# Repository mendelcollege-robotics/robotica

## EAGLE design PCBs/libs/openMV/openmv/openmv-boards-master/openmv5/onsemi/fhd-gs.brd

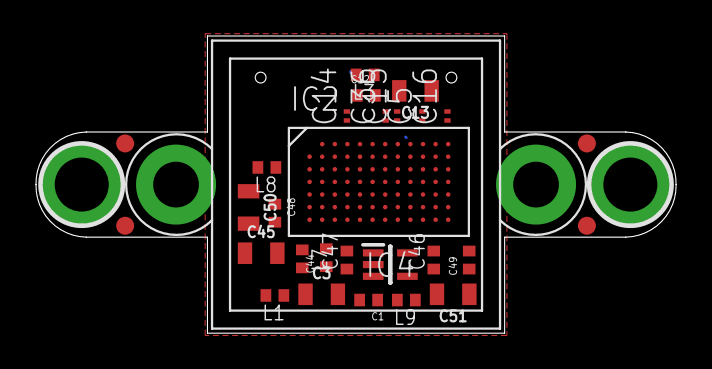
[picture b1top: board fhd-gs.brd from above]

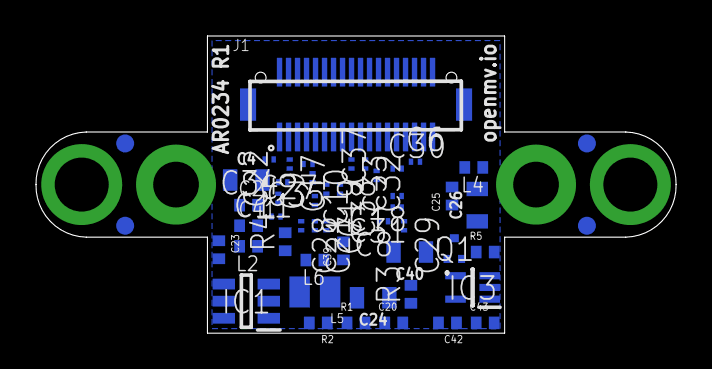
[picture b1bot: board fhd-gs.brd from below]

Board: 6 copper layers, 35.6 x 16.5 mm, 80 parts (51 on the bottom side), 40 nets.

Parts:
C1, C2, C12, C23, C25, C39, C41, C42, C43, C44, C46, C47, C48, C49: 4.7uF; 0402
C3, C4, C13, C24, C26, C40, C45, C50, C51: 22uF; 0805
C5, C6, C7, C8, C9, C10, C11, C14, C15, C16, C17, C18, C19, C21, C22, C27, C28, C29, C30, C31, C32, C33, C34, C35, C36, C37, C38: 0.22uF; C0201
C20: 6.8pF; 0402
FD1, FD2, FD3, FD4, FD5, FD6, FD7, FD8: FIDUCIAL1X2; FIDUCIAL-1X2
H1: LENSMOUNT20MM; LENSMOUNT-20MM
IC1: TLV62568PDDCR; SOT95P280X110-6N
IC2: AR0234CSSC00SUKA0
IC3, IC4: MIC5365-2.8YC5-TR; SOT65P210X110-5N
J1: DF12-36-DP
L1, L2, L3, L4, L6, L7, L8, L9: 100; 0402
L5: MAKK2016T2R2M; INDC2016X100N
Q1: SSM3J15FV,L3F; SSM3J15FVL3F
R1, R2, R5: 100K; R0402
R3: 10K; R0402
R4: 1.5K; R0402

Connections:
CAP: C41.2, IC2.P$71
DCMI_CLK: IC2.P$82, J1.12
DCMI_D0: IC2.P$62, J1.9
DCMI_D1: IC2.P$75, J1.7
DCMI_D2: IC2.P$76, J1.31
DCMI_D3: IC2.P$50, J1.29
DCMI_D4: IC2.P$36, J1.35
DCMI_D5: IC2.P$37, J1.28
DCMI_D6: IC2.P$14, J1.26
DCMI_D7: IC2.P$51, J1.33
DCMI_D8: IC2.P$39, J1.24
DCMI_D9: IC2.P$27, J1.22
DCMI_FSIN: IC2.P$40, J1.23
DCMI_HSYNC: IC2.P$30, J1.18
DCMI_PCLK: IC2.P$29, J1.14
DCMI_PWDN: J1.25, Q1.1
DCMI_PWDN_INT: IC3.3, Q1.3, R5.1
DCMI_RST: J1.21, R3.2
DCMI_SCL: IC2.P$65, J1.32
DCMI_SDA: IC2.P$53, J1.34
DCMI_VSYNC: IC2.P$18, J1.16
FB: C20.2, IC1.6, R1.1, R2.1
GND: C1.1, C2.1, C3.1, C4.1, C5.2, C6.2, C7.2, C8.2, C9.2, C10.2, C11.2, C12.1, C13.1, C14.2, C15.2, C16.2, C17.2, C18.2, C19.2, C21.2, C22.2, C23.1, C24.1, C25.1, C26.1, C27.2, C28.2, C29.2, C30.2, C31.2, C32.2, C33.2, C34.2, C35.2, C36.2, C37.2, C38.2, C39.1, C40.1, C41.1, C42.1, C43.1, C44.1, C45.1, C46.1, C47.1, C48.1, C49.1, C50.1, C51.1, IC1.2, IC2.P$1, IC2.P$2, IC2.P$4, IC2.P$5, IC2.P$8, IC2.P$13, IC2.P$17, IC2.P$23, IC2.P$24, IC2.P$26, IC2.P$28, IC2.P$43, IC2.P$44, IC2.P$49, IC2.P$54, IC2.P$55, IC2.P$61, IC2.P$64, IC2.P$68, IC2.P$74, IC2.P$77, IC2.P$81, IC3.2, IC4.2, J1.1, J1.3, J1.5, J1.6, J1.8, J1.19, J1.27, R2.2, R4.1, R5.2
RESET_N: IC1.5, IC2.P$66, R3.1
RSVD: IC2.P$69, R4.2
SPI_MISO: IC2.P$52, J1.15
SW: IC1.3, L5.2
VAA: C5.1, C6.1, C7.1, C8.1, C44.2, C45.2, IC2.P$9, IC2.P$12, IC2.P$73, IC2.P$78, L7.1
VAA_PHY: C9.1, C39.2, C40.2, IC2.P$67, L6.1
VAA_PIX: C27.1, C28.1, C29.1, C30.1, C48.2, C50.2, IC2.P$19, IC2.P$25, IC2.P$72, IC2.P$80, L8.1
VCC: C23.2, IC1.4, J1.2, J1.10, J1.20, J1.30, J1.36
VDD: C1.2, C3.2, C14.1, C15.1, C16.1, C17.1, C18.1, C19.1, C21.1, IC2.P$3, IC2.P$7, IC2.P$11, IC2.P$21, IC2.P$42, IC2.P$48, IC2.P$79, L1.1
VDDA: C43.2, C47.2, IC3.1, IC4.1, J1.4, Q1.2
VDDIO: C31.1, C32.1, C33.1, C34.1, C35.1, C36.1, C37.1, C38.1, C49.2, C51.2, IC2.P$6, IC2.P$15, IC2.P$16, IC2.P$22, IC2.P$38, IC2.P$41, IC2.P$60, IC2.P$83, L9.1
VDDIO_PHY: C11.1, C25.2, C26.2, IC2.P$45, L4.1
VDDIO_PHY_REG: C46.2, IC1.1, IC4.5, L4.2
VDDIO_REG: C42.2, IC3.5, IC4.3, L6.2, L7.2, L8.2, L9.2
VDD_DATA: C2.2, C4.2, C22.1, IC2.P$70, L2.1
VDD_PHY: C10.1, C12.2, C13.2, IC2.P$31, L3.1
VDD_REG: C20.1, C24.2, L1.2, L2.2, L3.2, L5.1, R1.2

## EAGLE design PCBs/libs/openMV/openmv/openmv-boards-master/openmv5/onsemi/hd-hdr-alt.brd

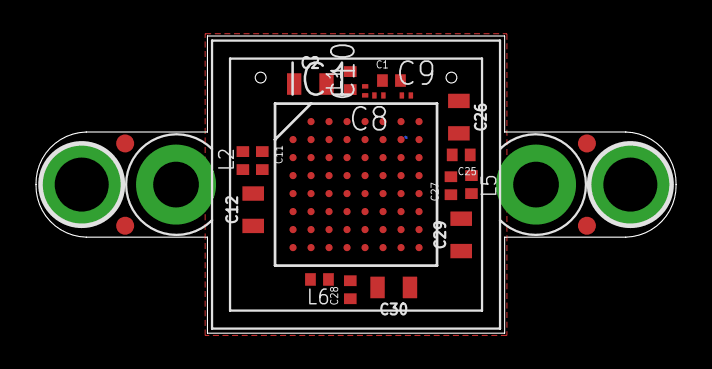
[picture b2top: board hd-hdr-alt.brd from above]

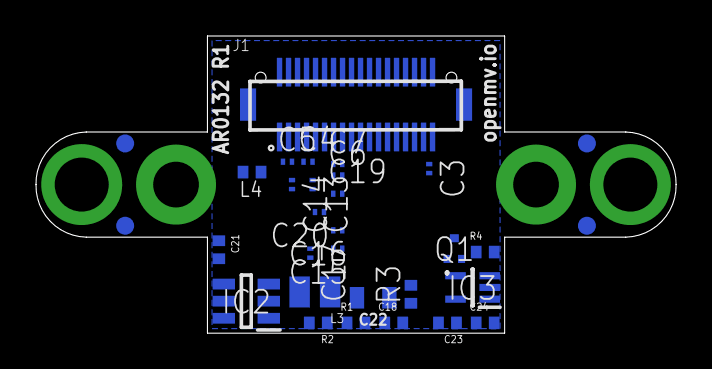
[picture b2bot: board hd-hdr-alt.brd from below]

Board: 6 copper layers, 35.6 x 16.5 mm, 54 parts (31 on the bottom side), 36 nets.

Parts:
C1, C11, C21, C23, C24, C25, C27, C28: 4.7uF; 0402
C2, C12, C22, C26, C29, C30: 22uF; 0805
C3, C4, C5, C6, C7, C8, C9, C10, C13, C14, C15, C16, C17, C19, C20: 0.22uF; C0201
C18: 6.8pF; 0402
FD1, FD2, FD3, FD4, FD5, FD6, FD7, FD8: FIDUCIAL1X2; FIDUCIAL-1X2
H1: LENSMOUNT20MM; LENSMOUNT-20MM
IC1: AR0132AT6C00XPEA0
IC2: TLV62568PDDCR; SOT95P280X110-6N
IC3: MIC5365-2.8YC5-TR; SOT65P210X110-5N
J1: DF12-36-DP
L1, L2, L4, L5, L6: 100; 0402
L3: MAKK2016T2R2M; INDC2016X100N
Q1: SSM3J15FV,L3F; SSM3J15FVL3F
R1: 200K; R0402
R2, R4: 100K; R0402
R3: 10K; R0402

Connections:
DCMI_CLK: IC1.P$16, J1.12
DCMI_D0: IC1.P$56, J1.3
DCMI_D1: IC1.P$57, J1.1
DCMI_D2: IC1.P$58, J1.9
DCMI_D3: IC1.P$59, J1.7
DCMI_D4: IC1.P$48, J1.31
DCMI_D5: IC1.P$49, J1.29
DCMI_D6: IC1.P$50, J1.35
DCMI_D7: IC1.P$51, J1.28
DCMI_D8: IC1.P$40, J1.26
DCMI_D9: IC1.P$41, J1.33
DCMI_D10: IC1.P$42, J1.24
DCMI_D11: IC1.P$43, J1.22
DCMI_FSIN: IC1.P$54, J1.23
DCMI_HSYNC: IC1.P$32, J1.18
DCMI_PCLK: IC1.P$34, J1.14
DCMI_PWDN: J1.25, Q1.1
DCMI_PWDN_INT: IC3.3, Q1.3, R4.1
DCMI_RST: J1.21, R3.2
DCMI_SCL: IC1.P$25, J1.32
DCMI_SDA: IC1.P$26, J1.34
DCMI_VSYNC: IC1.P$33, J1.16
FB: C18.2, IC2.6, R1.1, R2.1
GND: C1.1, C2.1, C3.2, C4.2, C5.2, C6.2, C7.2, C8.2, C9.2, C10.2, C11.1, C12.1, C13.2, C14.2, C15.2, C16.2, C17.2, C19.2, C20.2, C21.1, C22.1, C23.1, C24.1, C25.1, C26.1, C27.1, C28.1, C29.1, C30.1, IC1.P$7, IC1.P$20, IC1.P$22, IC1.P$23, IC1.P$24, IC1.P$27, IC1.P$28, IC1.P$36, IC1.P$44, IC1.P$46, IC1.P$52, IC1.P$55, IC1.P$60, IC2.2, IC3.2, J1.5, J1.6, J1.8, J1.19, J1.27, R2.2, R4.2
RESET_N: IC1.P$63, IC2.5, R3.1
SPI_MISO: IC1.P$35, J1.15
SW: IC2.3, L3.2
VAA: C4.1, C5.1, C25.2, C26.2, IC1.P$14, IC1.P$15, L4.1
VAA_PIX: C13.1, C14.1, C27.2, C29.2, IC1.P$30, IC1.P$31, L5.1
VCC: C21.2, IC2.4, J1.2, J1.10, J1.20, J1.30, J1.36
VDD: C1.2, C2.2, C6.1, C7.1, C8.1, C9.1, C10.1, IC1.P$5, IC1.P$6, IC1.P$13, IC1.P$21, IC1.P$29, L1.1
VDDA: C24.2, IC3.1, J1.4, Q1.2
VDDIO: C15.1, C16.1, C17.1, C19.1, C20.1, C28.2, C30.2, IC1.P$37, IC1.P$45, IC1.P$53, IC1.P$61, IC1.P$62, L6.1
VDDIO_REG: C23.2, IC2.1, IC3.5, L2.2, L4.2, L5.2, L6.2
VDD_PLL: C3.1, C11.2, C12.2, IC1.P$8, L2.1
VDD_REG: C18.1, C22.2, L1.2, L3.1, R1.2

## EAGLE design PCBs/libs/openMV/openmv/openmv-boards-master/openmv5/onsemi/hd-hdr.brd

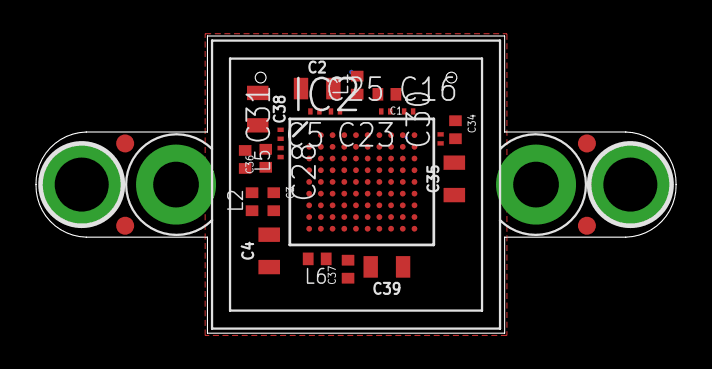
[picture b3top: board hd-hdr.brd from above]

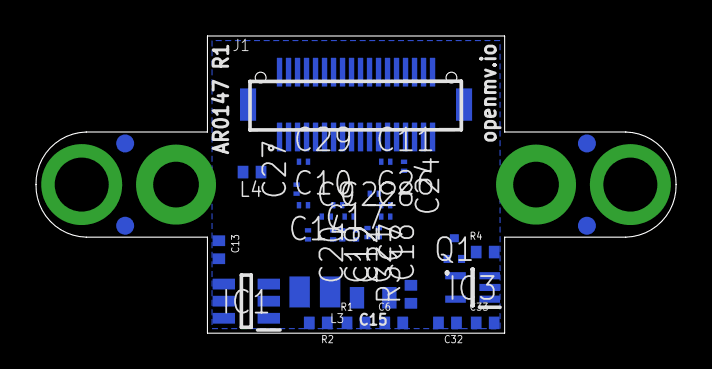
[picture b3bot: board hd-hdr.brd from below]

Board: 6 copper layers, 35.6 x 16.5 mm, 63 parts (36 on the bottom side), 36 nets.

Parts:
C1, C3, C13, C32, C33, C34, C36, C37: 4.7uF; 0402
C2, C4, C15, C35, C38, C39: 22uF; 0805
C5, C7, C8, C9, C10, C11, C12, C14, C16, C17, C18, C19, C20, C21, C22, C23, C24, C25, C26, C27, C28, C29, C30, C31: 0.22uF; C0201
C6: 6.8pF; 0402
FD1, FD2, FD3, FD4, FD5, FD6, FD7, FD8: FIDUCIAL1X2; FIDUCIAL-1X2
H1: LENSMOUNT20MM; LENSMOUNT-20MM
IC1: TLV62568PDDCR; SOT95P280X110-6N
IC2: AR0147ATSC00XUEG5
IC3: MIC5365-2.8YC5-TR; SOT65P210X110-5N
J1: DF12-36-DP
L1, L2, L4, L5, L6: 100; 0402
L3: MAKK2016T2R2M; INDC2016X100N
Q1: SSM3J15FV,L3F; SSM3J15FVL3F
R1, R2, R4: 100K; R0402
R3: 10K; R0402

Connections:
DCMI_CLK: IC2.P$43, J1.12
DCMI_D0: IC2.P$81, J1.3
DCMI_D1: IC2.P$32, J1.1
DCMI_D2: IC2.P$73, J1.9
DCMI_D3: IC2.P$63, J1.7
DCMI_D4: IC2.P$13, J1.31
DCMI_D5: IC2.P$54, J1.29
DCMI_D6: IC2.P$74, J1.35
DCMI_D7: IC2.P$34, J1.28
DCMI_D8: IC2.P$56, J1.26
DCMI_D9: IC2.P$45, J1.33
DCMI_D10: IC2.P$25, J1.24
DCMI_D11: IC2.P$36, J1.22
DCMI_FSIN: IC2.P$79, J1.23
DCMI_HSYNC: IC2.P$57, J1.18
DCMI_PCLK: IC2.P$23, J1.14
DCMI_PWDN: J1.25, Q1.1
DCMI_PWDN_INT: IC3.3, Q1.3, R4.1
DCMI_RST: J1.21, R3.2
DCMI_SCL: IC2.P$15, J1.32
DCMI_SDA: IC2.P$27, J1.34
DCMI_VSYNC: IC2.P$67, J1.16
FB: C6.2, IC1.6, R1.1, R2.1
GND: C1.1, C2.1, C3.1, C4.1, C5.2, C7.2, C8.2, C9.2, C10.2, C11.2, C12.2, C13.1, C14.2, C15.1, C16.2, C17.2, C18.2, C19.2, C20.2, C21.2, C22.2, C23.2, C24.2, C25.2, C26.2, C27.2, C28.2, C29.2, C30.2, C31.2, C32.1, C33.1, C34.1, C35.1, C36.1, C37.1, C38.1, C39.1, IC1.2, IC2.P$3, IC2.P$9, IC2.P$12, IC2.P$16, IC2.P$17, IC2.P$18, IC2.P$24, IC2.P$26, IC2.P$28, IC2.P$33, IC2.P$35, IC2.P$38, IC2.P$42, IC2.P$44, IC2.P$46, IC2.P$48, IC2.P$49, IC2.P$53, IC2.P$55, IC2.P$64, IC2.P$66, IC2.P$76, IC2.P$80, IC2.P$89, IC3.2, J1.5, J1.6, J1.8, J1.19, J1.27, R2.2, R4.2
RESET_N: IC1.5, IC2.P$47, R3.1
SPI_MISO: IC2.P$78, J1.15
SW: IC1.3, L3.2
VAA: C28.1, C29.1, C30.1, C34.2, C35.2, IC2.P$10, IC2.P$19, IC2.P$29, L4.1
VAA_PIX: C31.1, C36.2, C38.2, IC2.P$11, L5.1
VCC: C13.2, IC1.4, J1.2, J1.10, J1.20, J1.30, J1.36
VDD: C1.2, C2.2, C5.1, C7.1, C8.1, C9.1, C10.1, C11.1, C12.1, C14.1, C16.1, IC2.P$1, IC2.P$8, IC2.P$22, IC2.P$65, IC2.P$69, IC2.P$72, IC2.P$77, IC2.P$83, IC2.P$85, L1.1
VDDA: C33.2, IC3.1, J1.4, Q1.2
VDDIO: C18.1, C19.1, C20.1, C21.1, C22.1, C23.1, C24.1, C25.1, C26.1, C27.1, C37.2, C39.2, IC2.P$2, IC2.P$7, IC2.P$20, IC2.P$59, IC2.P$62, IC2.P$75, IC2.P$82, IC2.P$84, IC2.P$86, IC2.P$88, L6.1
VDDIO_REG: C32.2, IC1.1, IC3.5, L4.2, L5.2, L6.2
VDD_PHY: C3.2, C4.2, C17.1, IC2.P$52, L2.1
VDD_REG: C6.1, C15.2, L1.2, L2.2, L3.1, R1.2

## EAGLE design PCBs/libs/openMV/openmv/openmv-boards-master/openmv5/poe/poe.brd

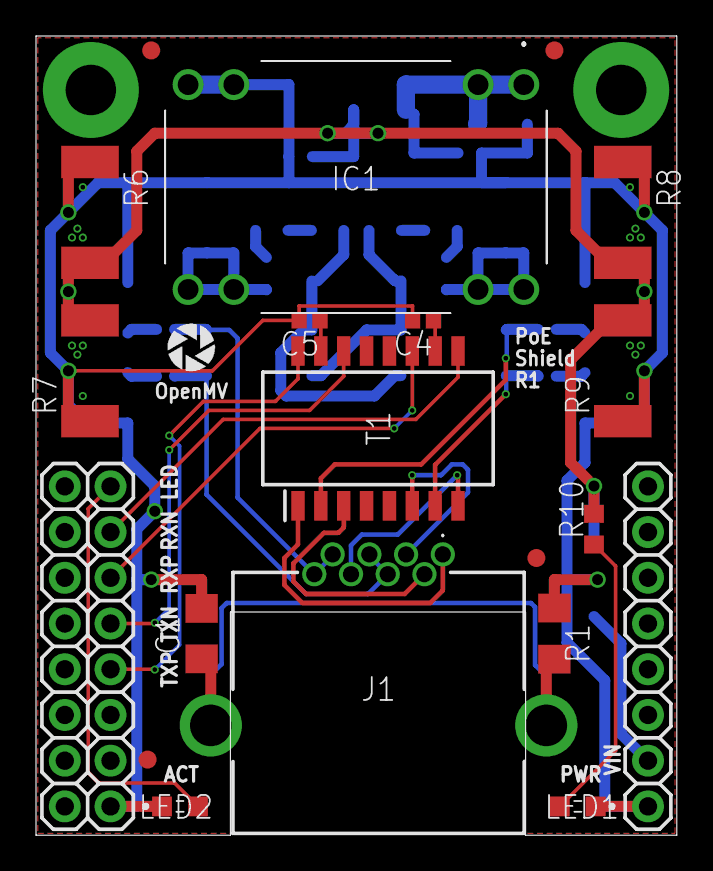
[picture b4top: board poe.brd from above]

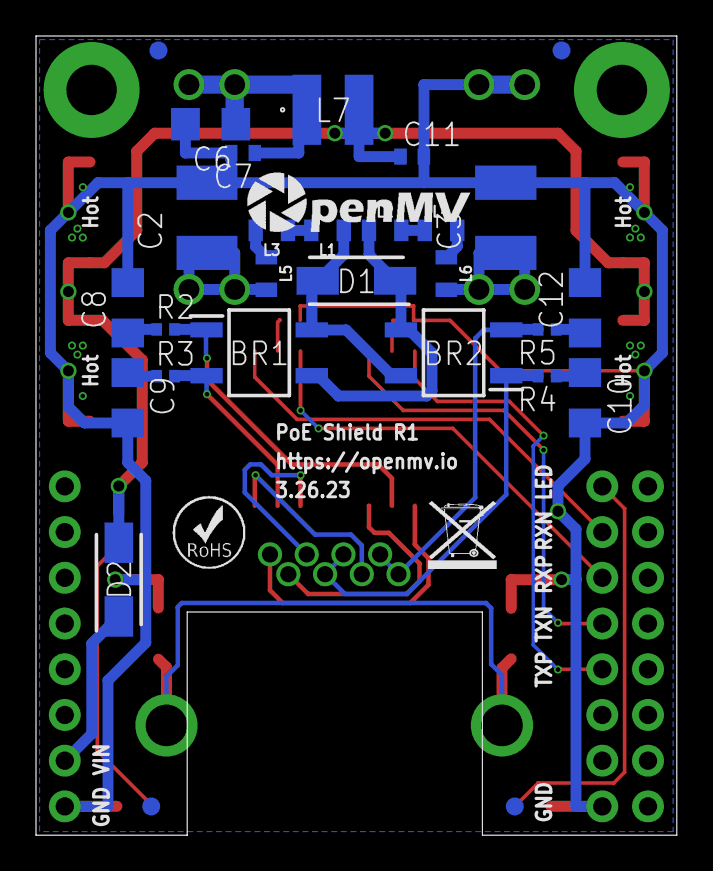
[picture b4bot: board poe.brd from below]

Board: 2 copper layers, 35.6 x 44.4 mm, 51 parts (31 on the bottom side), 33 nets.

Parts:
BR1, BR2: MB6S-TP; SOP254P665X270-4N
C1, C8, C9, C10, C12: 1nF; C1206
C2, C3: 4.7nF; C1812
C4, C5: 0.1uF; 0402
C6: 100uF; C1206
C7, C11: 10uF; C0402
D1: SMAJ58A-13-F; DIOM5226X230N
D2: FM240A; DIOM5025X231N
FD1, FD2, FD3, FD4, FD5, FD6, FD7, FD8: FIDUCIAL1X2; FIDUCIAL-1X2
IC1: AG9905LP
J1: GMJXHT-MM-S-88; GMJXHTMMS88
J2: OPENMV5-BOTTOM
L1, L2, L3, L4, L5, L6: 1K; 0805
L7: VLCF4020T-1R8N1R9; VLCF4020
LED1: LTST-S270KSKT; LTSTS270K
LED2: LTST-S270KGKT; LTSTS270K
R1: 1M; R1206
R2, R3, R4, R5: 75; R0402
R6, R7, R8, R9: 100; R2512
R10: 470; R0603
T1: PT61018PEL; SOIC127P930X565-16N
U$1: WEEE
U$2: ROHS
U$3: OMV-LOGO
U$9: OPENMV-LOGO

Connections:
GND: C1.2, C2.2, C3.2, C4.2, C5.2, C6.2, C7.2, C8.2, C9.2, C10.2, C11.2, C12.2, IC1.3, IC1.4, J2.9, J2.24, LED1.1, LED2.1, R1.1, R6.1, R7.1, R8.1, R9.1
MDI_LED: J2.17, LED2.2
MDI_RX_CT: C4.1, T1.10
MDI_RX_N: J2.18, T1.9
MDI_RX_P: J2.19, T1.11
MDI_TX_CT: C5.1, T1.15
MDI_TX_N: J2.20, T1.14
MDI_TX_P: J2.21, T1.16
POE_VIN_INT_N: C2.1, IC1.7, IC1.8, L5.2
POE_VIN_INT_P: C3.1, IC1.5, IC1.6, L6.2
POE_VIN_N: BR1.4, BR2.4, D1.2, L1.1
POE_VIN_N0: L1.2, L3.1
POE_VIN_N1: L3.2, L5.1
POE_VIN_P: BR1.3, BR2.3, D1.1, L2.1
POE_VIN_P0: L2.2, L4.1
POE_VIN_P1: L4.2, L6.1
RX_N: J1.6, T1.8
RX_P: J1.3, T1.6
SHIELD_GND: C1.1, J1.MH1, J1.MH2, R1.2
TX_N: J1.2, T1.3
TX_P: J1.1, T1.1
VA1: BR1.1, R2.2, T1.2
VA1_ISO: C8.1, R2.1
VA2: BR1.2, R3.2, T1.7
VA2_ISO: C9.1, R3.1
VB1: BR2.1, J1.4, J1.5, R4.2
VB1_ISO: C10.1, R4.1
VB2: BR2.2, J1.7, J1.8, R5.2
VB2_ISO: C12.1, R5.1
VDC: C6.1, C7.1, IC1.1, IC1.2, L7.1
VIN: C11.1, D2.2, L7.2, R6.2, R7.2, R8.2, R9.2, R10.2
VIN_INT: D2.1, J2.10
VIN_LED: LED1.2, R10.1

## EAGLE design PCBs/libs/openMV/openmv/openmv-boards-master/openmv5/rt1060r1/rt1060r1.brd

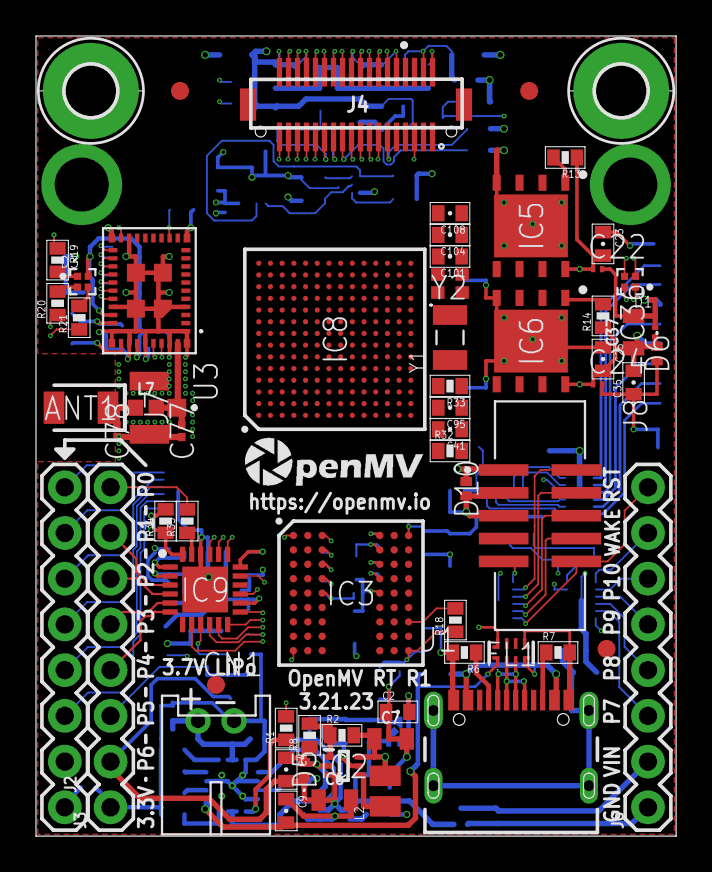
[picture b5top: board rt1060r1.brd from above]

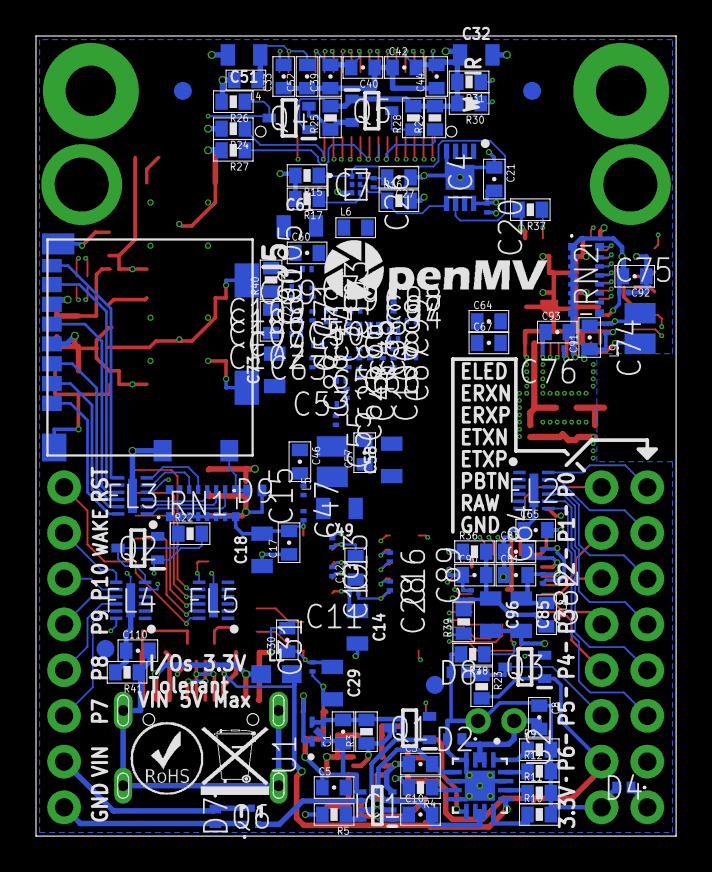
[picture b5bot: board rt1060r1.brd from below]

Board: 8 copper layers, 35.6 x 44.4 mm, 222 parts (153 on the bottom side), 216 nets.

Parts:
ANT1: AMCA31-2R450G-S1F-T3; ANTC3216X140N
C1, C2, C3, C4, C5, C8, C9, C10, C12, C17, C21, C23, C25, C27, C30, C33, C35, C39, C40, C41, C42, C44, C46, C52, C57, C60, C64, C65, C67, C72, C81, C83, C90, C91, C92, C93, C95, C101, C104, C108: 4.7uF; 0402-CAP
C6, C7, C14, C18, C29, C32, C37, C49, C51, C58, C61, C73, C85, C96: 22uF; 0805
C11, C13, C15, C16, C19, C20, C22, C24, C26, C28, C31, C34, C36, C38, C43, C45, C47, C48, C50, C53, C54, C55, C56, C59, C62, C63, C66, C68, C69, C70, C71, C74, C75, C76, C82, C84, C86, C87, C88, C89, C94, C97, C98, C99, C100, C102, C103, C107, C109: 0.22uF; C0201
C77: GRM0335C1H1R5BA01D; CAPC0603X33N
C78: DNP; CAPC0603X33N
C79, C80: 18pF; C0201
C105, C106: 4.7pF; C0201
C110: 1nF; 0402-CAP
CN1: S2B-PH-K-S(LF)(SN); JST-PH-2-THM-RA
D1, D3: UHD1110-FKA-CL1A13R3Q1BBQFMF3; LED_UHD1110-FKA-CL1A13R3Q1BBQFMF3
D2, D4, D5, D6, D7, D8, D9, D10: CPDQT5V0HE-HF; CPDQT5V0HEHF
FD1, FD2, FD3, FD4, FD5, FD6, FD7, FD8: FIDUCIAL1X2; FIDUCIAL-1X2
FL1: ECMF02-4CMX8; ECMF024CMX8
FL2, FL3, FL4, FL5: EMIF06-1005M12; SON40P150X250X65-13N
H1, H2: MOUNT-PAD-ROUND2.8; 2,8-PAD
IC1: LM66200DRLR; SOTFL50P160X60-8N
IC2: AP61300Z6-7; SOTFL50P162X60-6N
IC3: IS42S16160G-6BL; BGA54C80P9X9_800X800X120
IC4: ATECC608B-MAHDA-T; SON50P300X200X60-9N
IC5: IS25LP064D-JKLE-TR; SON127P500X595X80-9N
IC6: IS25LP128F-JKLE-TR; SON127P500X595X80-9N
IC7: MXC4005XC
IC8: MIMXRT106FCVL5B; BGA196C65P14X14_1000X1000X143
IC9: KSZ8081RNDCA-TR; QFN50P400X400X90-25N
J1: USB4105-GF-A; GCT_USB4105-GF-A
J2, J3, J6: DNP; 1X08
J4: DF12-36-DS
J5: USD-1040310811; 1040310811
J7: DNP; 23370191
J8: 3221-10-0300-00; CNC_3221-10-0300-00
L1: 100; 0603
L2: MAKK2016T1R0M; INDC2016X100N
L4, L6, L8: 100; C0402
L5: MAKK2016T4R7M; INDC2016X100N
L7: 3.9NH; 0402
L9: MAKK2016T2R2M; INDC2016X100N
M1, M2: 9774030151R
Q1, Q2, Q3, Q4, Q5: 2N7002KW_R1_00001; SOT65P210X110-3N
Q6: PMXB120EPEZ
R1, R4, R5, R26, R36, R39: 1K; 0402-RES
R2: 200K; 0402-RES
R3, R13, R14, R18, R22, R23, R24, R25, R27, R28, R29, R34: 100K; 0402-RES
R6, R7: 5.1K; 0402-RES
R8: 44.2K; 0402-RES
R9, R33, R37: 10K; 0402-RES
R10: 3.3K; 0402-RES
R11: 46.4K; 0402-RES
R12: 8.2K; 0402-RES
R15, R16, R17: 2.7K; 0402-RES
R19, R20, R21, R35: 220; 0402-RES
R30, R31: 4.7K; 0402-RES
R32: 30K; 0402-RES
R38: 6.49K; 0402-RES
R40: 2.2M; 0402-RES
R41: 1M; 0402-RES
RN1, RN2: EXB-2HV104JV; EXB2HV104JV
U1: MIC5365-3.3YMT-TZ; VREG_MIC5365-3.3YMT-TZ
U2: BQ24075RGTR; QFN50P300X300X100-17N
U3: LBEE5KL1DX-883; XCVR_LBEE5KL1DX-TEMP
U$1: WEEE
U$2: ROHS
U$3: OMV-LOGO
U$4: OMV-LOGO-SMALL
Y1: SC32S-7PF20PPM; XTAL_ABS07-32.768KHZ-7-T
Y2: XRCGB24M000F3M00R0

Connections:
ANT: C77.1, J7.1, L7.2, U3.41
BAT: C8.2, CN1.1, D2.1, U2.2, U2.3
BT_D_WAKE: IC8.L7, U3.39
BT_H_WAKE: IC8.H14, U3.38
BT_REG_ON: IC8.F13, R37.1, U3.14
BT_UART_RX: IC8.C9, U3.3
BT_UART_TX: IC8.B9, U3.2
CC1: J1.A5, R6.1
CC2: J1.B5, R7.1
CHG: R1.1, U2.9
DCDC_LP: IC8.M1, IC8.M2, L5.2
DCDC_PSWITCH: C62.1, IC8.K3, R32.1
DCMI_CLK: IC8.B14, J4.12
DCMI_D0: IC8.J14, J4.31
DCMI_D1: IC8.G12, J4.29
DCMI_D2: IC8.H11, J4.35
DCMI_D3: IC8.H12, J4.28
DCMI_D4: IC8.J13, J4.26
DCMI_D5: IC8.L13, J4.33
DCMI_D6: IC8.G14, J4.24
DCMI_D7: IC8.F11, J4.22
DCMI_FSIN: J4.23, Q5.3, R28.1
DCMI_HSYNC: IC8.L10, J4.18
DCMI_MISO: IC8.E7, J4.15
DCMI_MOSI: IC8.E8, J4.17
DCMI_PCLK: IC8.D13, J4.14
DCMI_PWDN: IC8.C11, J4.25, R29.1
DCMI_RST: IC8.B11, J4.21, R27.1
DCMI_SCL: IC8.J11, J4.32, R30.1
DCMI_SCLK: IC8.D8, J4.13
DCMI_SDA: IC8.K11, J4.34, R31.1
DCMI_SSEL: IC8.D7, J4.11, R24.1
DCMI_VSYNC: IC8.D14, J4.16
D_N: FL1.3, J1.A7, J1.B7
D_P: FL1.2, J1.A6, J1.B6
EN: IC2.5, Q1.3, R3.1
ETH_INT: IC8.C10, IC9.18, R36.1
ETH_LED: IC9.23, R35.1
ETH_MDC: IC8.A7, IC9.11
ETH_MDIO: IC8.C7, IC9.10, R39.1
ETH_RST: C65.2, IC8.D10, IC9.24, R34.1
ETH_RXD0: IC8.E12, IC9.13
ETH_RXD1: IC8.D12, IC9.12
ETH_RXDV: IC8.C12, IC9.15
ETH_RXERR: IC8.C13, IC9.17
ETH_TXCLK: IC8.B13, IC9.8
ETH_TXD0: IC8.B12, IC9.20
ETH_TXD1: IC8.A12, IC9.21
ETH_TXEN: IC8.A13, IC9.19
ETH_VDDA_3.3: C81.2, C82.1, C85.1, IC9.2, L8.1
ETH_VDD_1.2: C83.2, C84.1, IC9.1
FB: IC2.1, R2.1, R8.2
FEED: ANT1.1, C78.1, L7.1
GND: C1.1, C2.1, C3.1, C4.1, C5.1, C6.2, C7.2, C8.1, C9.1, C10.1, C11.1, C12.2, C13.2, C14.2, C15.2, C16.2, C17.1, C18.1, C19.2, C20.2, C21.1, C22.2, C23.1, C24.2, C25.1, C26.2, C27.1, C28.2, C29.2, C30.2, C31.1, C32.2, C33.1, C34.2, C35.1, C36.2, C37.2, C38.2, C39.1, C40.1, C41.1, C42.1, C43.2, C44.1, C45.2, C46.1, C47.2, C48.2, C49.1, C50.2, C51.2, C52.1, C53.2, C54.2, C55.2, C56.2, C57.1, C58.1, C59.2, C60.1, C61.1, C62.2, C63.2, C64.2, C65.1, C66.1, C67.2, C68.1, C69.2, C70.2, C71.2, C72.1, C73.1, C74.2, C75.2, C76.2, C77.2, C78.2, C79.2, C80.2, C81.1, C82.2, C83.1, C84.2, C85.2, C86.1, C87.1, C88.2, C89.2, C90.1, C91.1, C92.1, C93.1, C94.1, C95.1, C96.2, C97.1, C98.1, C99.1, C100.1, C101.1, C102.2, C103.1, C104.1, C105.2, C106.2, C107.2, C108.1, C109.2, C110.1, CN1.2, D2.2, D4.2, D5.2, D6.2, D7.2, D8.2, D9.2, D10.2, FL1.5, FL1.8, FL2.13, FL3.13, FL4.13, FL5.13, IC1.1, IC1.4, IC1.5, IC2.2, IC3.A1, IC3.A3, IC3.B7, IC3.C3, IC3.D7, IC3.E3, IC3.J1, IC4.4, IC4.9, IC5.4, IC5.9, IC6.4, IC6.9, IC7.3, IC8.A1, IC8.A14, IC8.B5, IC8.B10, IC8.E2, IC8.E13, IC8.G7, IC8.G8, IC8.H7, IC8.H8, IC8.J7, IC8.J8, IC8.K2, IC8.K6, IC8.K9, IC8.K13, IC8.L9, IC8.N1, IC8.N2, IC8.N5, IC8.N8, IC8.P1, IC8.P14, IC9.22, IC9.25, J1.A1_B12, J1.B1_A12, J3.1, J4.5, J4.19, J4.27, J5.CD$2, J5.G$1, J5.G$2, J5.G$3, J5.G$4, J5.P$6, J6.1, J7.2, J7.3, J8.3, J8.5, Q6.1, R6.2, R7.2, R8.1, R9.2, R10.2, R11.2, R12.2, R27.2, R37.2, R38.2, R40.2, R41.2, U1.2, U1.EP, U2.4, U2.6, U2.8, U2.15, U2.17, U3.1, U3.4, U3.12, U3.19, U3.21, U3.29, U3.32, U3.33, U3.35, U3.37, U3.40, U3.42, U3.43, U3.44, U3.45, U3.46, Y2.2, Y2.4
ILIM: R10.1, U2.12
INT_I2C_INT: IC7.4, IC8.D11, R17.1
INT_I2C_SCL: IC4.6, IC7.1, IC8.C8, R15.1
INT_I2C_SDA: IC4.5, IC7.5, IC8.B8, R16.1
ISET: R12.1, U2.16
JTAG_TCK: FL5.4, IC8.F12
JTAG_TCK_INT: FL5.9, J8.4
JTAG_TDI: FL5.2, IC8.F14
JTAG_TDI_INT: FL5.11, J8.8
JTAG_TDO: FL5.3, IC8.G13
JTAG_TDO_INT: FL5.10, J8.6
JTAG_TMS: FL5.5, IC8.E14
JTAG_TMS_INT: FL5.8, J8.2
JTAG_TRSTB: FL5.6, IC8.G10
JTAG_TRSTB_INT: FL5.7, J8.9
LED_B: IC8.C14, R19.1
LED_B_INT: D3.1, R19.2
LED_CHG: D1.3, R1.2
LED_G: IC8.A10, R20.1
LED_G_INT: D3.2, R20.2
LED_PGOOD: D1.2, R4.2
LED_R: IC8.D9, R21.1
LED_R_INT: D3.3, R21.2
LED_ST: D1.1, R5.2
MDI_LED: J3.8, R35.2
MDI_RX_N: IC9.3, J3.7
MDI_RX_P: IC9.4, J3.6
MDI_TX_N: IC9.5, J3.5
MDI_TX_P: IC9.6, J3.4
NVCC_PLL: C104.2, C107.1, IC8.P10
ONOFF: IC8.M6, Q3.2
P0_MOSI: FL2.1, IC8.H10
P0_MOSI_INT: FL2.12, J2.8
P1_MISO: FL2.2, IC8.M11
P1_MISO_INT: FL2.11, J2.7
P2_SCLK: FL2.3, IC8.M14
P2_SCLK_INT: FL2.10, J2.6
P3_NSS: FL2.4, IC8.G11
P3_NSS_INT: FL2.9, J2.5
P4_SCL: FL2.5, IC8.K14
P4_SCL_INT: FL2.8, J2.4
P5_SDA: FL2.6, IC8.L14
P5_SDA_INT: FL2.7, J2.3
P6_ADC: FL4.1, IC8.M12
P6_ADC_INT: FL4.12, J2.2
P7_PWM: FL4.2, IC8.A8
P7_PWM_INT: FL4.11, J6.3
P8_PWM: FL4.3, IC8.A9
P8_PWM_INT: FL4.10, J6.4
P9_PWM: FL4.4, IC8.A11
P9_PWM_INT: FL4.9, J6.5
P10_PWM: FL4.5, Q4.3, R26.1
P10_PWM_INT: FL4.8, J6.6
P11_WAKEUP: FL4.6, Q2.3, R22.1
P11_WAKEUP_INT: FL4.7, J6.7
P12_RST_N: C63.1, FL5.1, IC8.M7, R33.2
P12_RST_N_EXT: FL5.12, J6.8, J8.10
PGOOD: R4.1, U2.7
PMIC_ONOFF: D8.1, J3.3, Q3.3, R23.1
PMIC_ON_REQ: IC8.K7, Q1.2
PWM_FSIN: IC8.B7, Q4.2, Q5.2, R25.1
P_FLASH_CE: IC5.1, IC8.L3, R13.2
P_FLASH_IO0: IC5.5, IC8.P3
P_FLASH_IO1: IC5.2, IC8.N4
P_FLASH_IO2: IC5.3, IC8.P4
P_FLASH_IO3: IC5.7, IC8.P5
P_FLASH_SCK: IC5.6, IC8.L4
RAW: C1.2, C4.2, C6.1, D1.4, D5.1, IC1.2, IC1.7, IC2.3, J3.2, Q1.1, Q2.1, Q3.1, R3.2, R22.2, R23.2, U1.3, U1.4
REXT: IC9.9, R38.1
RTC_XTALI: C80.1, IC8.N9, Y1.2
RTC_XTALO: C79.1, IC8.P9, Y1.1
SDRAM_A0: IC3.H7, IC8.C2
SDRAM_A1: IC3.H8, IC8.G1
SDRAM_A2: IC3.J8, IC8.G3
SDRAM_A3: IC3.J7, IC8.H1
SDRAM_A4: IC3.J3, IC8.A6
SDRAM_A5: IC3.J2, IC8.B6
SDRAM_A6: IC3.H3, IC8.B1
SDRAM_A7: IC3.H2, IC8.A5
SDRAM_A8: IC3.H1, IC8.A4
SDRAM_A9: IC3.G3, IC8.B2
SDRAM_A10: IC3.H9, IC8.G2
SDRAM_A11: IC3.G2, IC8.B4
SDRAM_A12: IC3.G1, IC8.A3
SDRAM_BA0: IC3.G7, IC8.C1
SDRAM_BA1: IC3.G8, IC8.F1
SDRAM_CAS: IC3.F7, IC8.D3
SDRAM_CKE: IC3.F3, IC8.A2
SDRAM_CLK: IC3.F2, IC8.B3
SDRAM_CS: IC3.G9, IC8.E1, R18.2
SDRAM_DQ0: IC3.A8, IC8.E3
SDRAM_DQ1: IC3.B9, IC8.F3
SDRAM_DQ2: IC3.B8, IC8.F4
SDRAM_DQ3: IC3.C9, IC8.G4
SDRAM_DQ4: IC3.C8, IC8.F2
SDRAM_DQ5: IC3.D9, IC8.G5
SDRAM_DQ6: IC3.D8, IC8.H5
SDRAM_DQ7: IC3.E9, IC8.H4
SDRAM_DQ8: IC3.E1, IC8.C6
SDRAM_DQ9: IC3.D2, IC8.C5
SDRAM_DQ10: IC3.D1, IC8.D5
SDRAM_DQ11: IC3.C2, IC8.C4
SDRAM_DQ12: IC3.C1, IC8.D4
SDRAM_DQ13: IC3.B2, IC8.E5
SDRAM_DQ14: IC3.B1, IC8.C3
SDRAM_DQ15: IC3.A2, IC8.E4
SDRAM_DQMH: IC3.F1, IC8.D6
SDRAM_DQML: IC3.E8, IC8.H3
SDRAM_RAS: IC3.F8, IC8.D2
SDRAM_WE: IC3.F9, IC8.D1
SD_CD: D9.1, IC8.L11, J5.CD$1, RN1.9
SD_CLK: FL3.4, IC8.J3
SD_CLK_INT: FL3.9, J5.P$5
SD_CMD: FL3.3, IC8.J4, RN1.12
SD_CMD_INT: FL3.10, J5.P$3
SD_DAT0: FL3.5, IC8.J1, RN1.14
SD_DAT0_INT: FL3.8, J5.P$7
SD_DAT1: FL3.6, IC8.K1, RN1.13
SD_DAT1_INT: FL3.7, J5.P$8
SD_DAT2: FL3.1, IC8.H2, RN1.10
SD_DAT2_INT: FL3.12, J5.P$1
SD_DAT3: FL3.2, IC8.J2, RN1.11
SD_DAT3_INT: FL3.11, J5.P$2
SHELL_GND: C110.2, J1.S1, J1.S2, J1.S3, J1.S4, R41.1
SR_VLX: L9.1, U3.34
ST: IC1.8, R5.1
SW: IC2.4, L2.1
S_FLASH_CE: IC6.1, IC8.N3, R14.2
S_FLASH_IO0: IC6.5, IC8.M4
S_FLASH_IO1: IC6.2, IC8.M3
S_FLASH_IO2: IC6.3, IC8.M5
S_FLASH_IO3: IC6.7, IC8.L5
S_FLASH_SCK: IC6.6, IC8.P2
TMR: R11.1, U2.14
TS: R9.1, U2.1
USB_D_N: FL1.6, IC8.M8
USB_D_P: FL1.7, IC8.L8
USB_VBUS: FL1.4, J1.A4_B9, J1.B4_A9, L1.1
VBUS: C9.2, C88.1, C95.2, FL1.1, IC8.N6, L1.2, U2.13
VCC: C7.1, C11.2, C12.1, C13.1, C14.1, C15.1, C16.1, C17.2, C18.2, C19.1, C20.1, C21.2, C22.1, C23.2, C24.1, C25.2, C26.1, C27.2, C28.1, C29.1, C30.1, C31.2, C32.1, C33.2, C35.2, C36.1, C37.1, C39.2, C40.2, C41.2, C42.2, C43.1, C44.2, C50.1, C53.1, C54.1, C55.1, C56.1, C57.2, C58.2, C64.1, C66.2, C67.1, C68.2, C75.1, C76.1, C86.2, C89.1, C90.2, C92.2, C93.2, C96.1, C99.2, C108.2, C109.1, D3.4, D4.1, D6.1, D10.1, IC2.6, IC3.A7, IC3.A9, IC3.B3, IC3.C7, IC3.D3, IC3.E7, IC3.J9, IC4.8, IC5.8, IC6.8, IC7.6, IC8.E6, IC8.E9, IC8.F5, IC8.F10, IC8.J6, IC8.J10, IC8.K4, IC8.K5, IC8.L1, IC8.L2, IC8.P12, IC9.14, J2.1, J4.2, J4.10, J4.20, J4.30, J4.36, J5.P$4, J8.1, L2.2, L4.2, L6.2, L8.2, Q4.1, Q5.1, R2.2, R13.1, R14.1, R15.2, R16.2, R17.2, R18.1, R24.2, R25.2, R26.2, R28.2, R29.2, R30.2, R31.2, R32.2, R33.1, R34.2, R36.2, R39.2, RN1.1, RN1.2, RN1.3, RN1.4, RN1.5, RN1.6, RN1.7, RN1.8, RN2.1, RN2.2, RN2.3, RN2.4, RN2.5, RN2.6, RN2.7, RN2.8, U3.30, U3.36
VCC_SOC: C34.1, C38.1, C45.1, C46.2, C47.1, C48.1, C49.2, C87.2, C94.2, C97.2, C98.2, C100.2, C103.2, IC8.F6, IC8.F7, IC8.F8, IC8.F9, IC8.G6, IC8.G9, IC8.H6, IC8.H9, IC8.J5, IC8.J9, L5.1
VDDA: C51.1, C52.2, J4.4, L4.1
VDDA_ADC_3P3: C59.1, C60.2, C61.2, IC8.N14, L6.1
VDD_HIGH_CAP: C101.2, C102.1, IC8.P8
VDD_SNVS: C2.2, C69.1, IC8.M9, U1.1
VDD_SNVS_CAP: C70.1, IC8.M10
VDD_USB_CAP: C71.1, C72.2, C73.2, IC8.K8
VIN: D7.1, J6.2, Q6.3
VIN_INT: C5.2, IC1.6, Q6.2
VIN_LDO: C74.1, C91.2, L9.2, U3.31
V_BATT: C3.2, C10.2, IC1.3, U2.5, U2.10, U2.11
WAKEUP: IC8.L6, Q2.2
WIFI_CLK: IC8.M13, U3.20
WIFI_CMD: IC8.H13, RN2.16, U3.22
WIFI_D0: IC8.L12, RN2.14, U3.24
WIFI_D1: IC8.K12, RN2.12, U3.26
WIFI_D2: IC8.J12, RN2.15, U3.23
WIFI_D3: IC8.K10, RN2.13, U3.25
WL_H_WAKE: IC8.E11, U3.27
WL_REG_ON: IC8.E10, U3.28
XTALI: C106.1, IC8.P11, R40.1, Y2.3
XTALO: C105.1, IC8.N11, Y2.1

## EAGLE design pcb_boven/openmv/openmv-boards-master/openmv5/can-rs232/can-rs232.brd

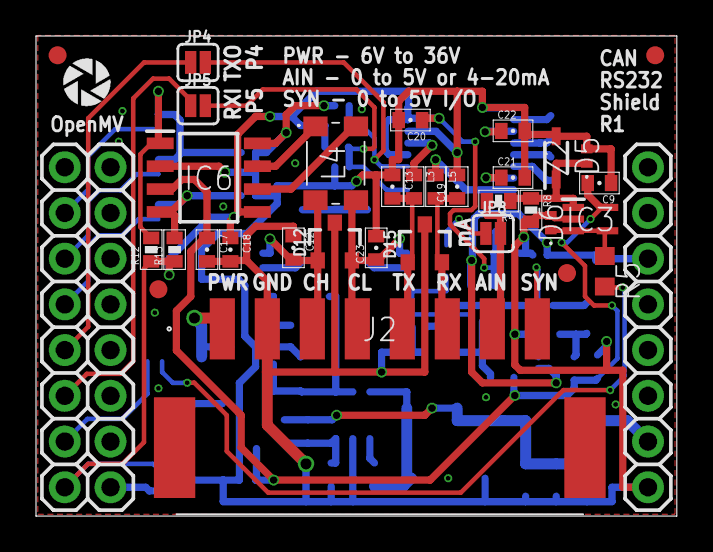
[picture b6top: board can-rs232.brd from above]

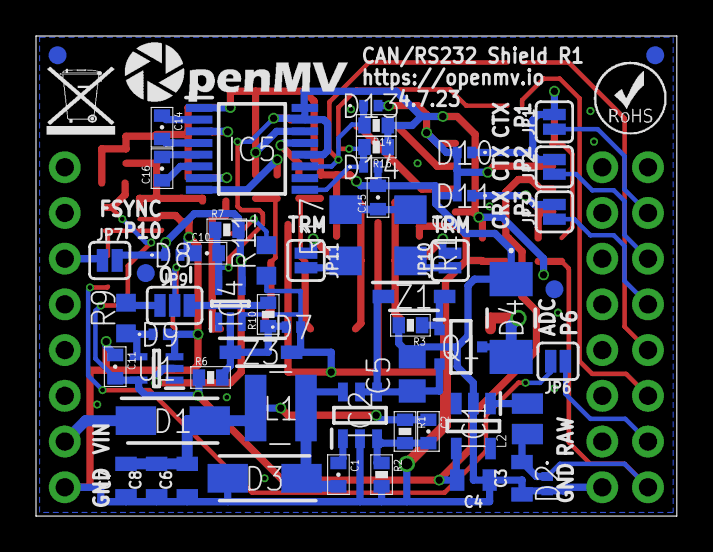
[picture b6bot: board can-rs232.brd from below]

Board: 2 copper layers, 35.6 x 26.7 mm, 96 parts (61 on the bottom side), 51 nets.

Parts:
C1, C9, C10, C11, C14, C16, C17, C18, C20, C21, C22: 0.1uF; 0402-CAP
C2, C12, C13, C19, C23: 100pF; 0402-CAP
C3, C4, C6, C7, C8: 22uF; 0805
C5: 10uF; C0805
C15: 4.7nF; 0402-CAP
D1, D3: FM240A; DIOM5025X231N
D2, D5, D6, D7, D8, D9, D10, D11, D13, D14: CPDQT5V0HE-HF; CPDQT5V0HEHF
D4: SMAJ40CAE3_TR13; SMAJ40CAE3TR13
D12, D15: PESD1CAN; SOT23-3
FD1, FD2, FD3, FD4, FD5, FD6, FD7, FD8: FIDUCIAL1X2; FIDUCIAL-1X2
IC1: TPS613222ADBVR; SOT95P280X145-5N
IC2: AP64060WU-7; SOT95P280X100-6N
IC3: LM321LVIDCKR; SOT65P210X110-5N
IC4: 74LVC1G07GW,125; SOT65P212X110-5N
IC5: SN65C3221EPWR; SOP65P640X120-16N
IC6: MCP2542FD-E_SN; SOIC127P600X175-8N
J1: OPENMV5-TOP
J2: 1771088
JP1, JP3, JP4, JP5, JP6, JP7, JP10, JP11: JUMPER-SMT_2_NC_PASTE_SILK; SMT-JUMPER_2_NC_PASTE_SILK
JP2, JP8: JUMPER-SMT_2_NO_SILK; SMT-JUMPER_2_NO_SILK
JP9: JUMPER-SMT_3_1-NC_PASTE_SILK; SMT-JUMPER_3_1-NC_PASTE_SILK
L1: NRS4018T100MDGJ
L2: MAKK2016T2R2M; INDC2016X100N
L3, L5: 100; C0402
L4: SRF4532-110Y; SRF4532101Y
Q1: SSM3J356R,LF; SOTFL95P240X88-3N
R1: 133K; 0402-RES
R2: 22.1K; 0402-RES
R3, R6, R7, R8: 100K; 0402-RES
R4: 51K; 0402-RES
R5, R9: 470; R0603
R10, R12, R13, R14, R15: 10K; 0402-RES
R11: 240; R0603
R16, R17: 60; R1206
U1: 74LVC1G17SE-7; SOT65P210X110-5N
U$1: WEEE
U$2: ROHS
U$3: OMV-LOGO
U$9: OPENMV-LOGO
Z1, Z3: MMSZ5231B-7-F; SOD3716X145N
Z2: DNP; SOD2512X110N

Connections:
AIN: J2.7, JP8.2, R4.2
AIN_INT: D5.1, IC3.1, R4.1, R8.1, Z2.1
AIN_OUT: D6.1, IC3.3, IC3.4, R5.1
AIN_S: JP8.1, R11.2
C1+: C14.1, IC5.2
C1-: C14.2, IC5.4
C2+: C16.2, IC5.5
C2-: C16.1, IC5.6
CANH: C12.2, D12.1, J2.3, JP10.2, L4.2
CANH_INT: IC6.7, L4.1
CANH_J: JP10.1, R16.2
CANL: C23.1, D12.2, J2.4, JP11.1, L4.3
CANL_INT: IC6.6, L4.4
CANL_J: JP11.2, R17.1
CAN_RX: D11.1, IC6.4, JP3.2, R13.2
CAN_RX_INT: J1.4, JP3.1
CAN_S: C15.1, R16.1, R17.2
CAN_TX: D10.1, IC6.1, JP1.2, JP2.2, R12.2
CAN_TX_INT: J1.2, JP1.1
CAN_TX_INT_2: J1.3, JP2.1
EXT_RXI: C19.1, D15.2, J2.6, L5.2
EXT_TXO: C13.2, D15.1, J2.5, L3.2
EXT_VIN: D4.2, J2.1, Q1.3
EXT_VIN_BST: C1.1, IC2.1
EXT_VIN_FB: C2.2, IC2.3, R1.2, R2.1
EXT_VIN_G: Q1.1, R3.1, Z1.2
EXT_VIN_INT: C5.1, IC2.4, IC2.5, Q1.2, Z1.1
EXT_VIN_OUT: C2.1, C6.2, C7.2, C8.2, D1.2, L1.2, R1.1
EXT_VIN_SW: C1.2, D3.1, IC2.6, L1.1
GND: C3.1, C4.1, C5.2, C6.1, C7.1, C8.1, C9.1, C10.1, C11.1, C12.1, C13.1, C15.2, C17.2, C18.2, C19.2, C20.2, C21.2, C22.2, C23.2, D2.2, D3.2, D4.1, D5.2, D6.2, D7.2, D8.2, D9.2, D10.2, D11.2, D12.3, D13.2, D14.2, D15.3, IC1.2, IC2.2, IC3.2, IC4.3, IC5.1, IC5.14, IC6.2, IC6.8, J1.9, J1.24, J2.2, R2.2, R3.2, R8.2, R11.1, U1.3, Z2.2, Z3.2
P6_ADC: JP6.2, R5.2
P6_ADC_INT: J1.7, JP6.1
P10_FSYNC: D8.1, IC4.4, JP7.2, R7.2, U1.2
P10_FSYNC_INT: J1.14, JP7.1
RS232_RXI: D14.1, IC5.9, JP5.2, R15.2
RS232_RXI_INT: J1.6, JP5.1
RS232_TXO: D13.1, IC5.11, JP4.2, R14.2
RS232_TXO_INT: J1.5, JP4.1
RXI: IC5.8, L5.1
SW: IC1.1, L2.2
SYNC: J2.8, JP9.2
SYNC_IN: JP9.3, R10.2
SYNC_IN_INT: D7.1, IC4.2, R6.2, R10.1, Z3.1
SYNC_OUT: JP9.1, R9.2
SYNC_OUT_INT: D9.1, R9.1, U1.4
TXO: IC5.13, L3.1
V+: C22.1, IC5.3
V-: C21.1, IC5.7
VCC: C3.2, C10.2, C18.1, C20.1, D2.1, IC4.5, IC5.12, IC5.15, IC5.16, IC6.5, J1.8, L2.1, R7.1, R12.1, R13.1, R14.1, R15.1
VIN: D1.1, J1.10
V_BATT: C4.2, C9.2, C11.2, C17.1, IC1.4, IC3.5, IC6.3, R6.1, U1.5

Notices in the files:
parts and their libraries:
SparkFun-Aesthetics: Licensing: Creative Commons ShareAlike 4.0 International - https://creativecommons.org/licenses/by-sa/4.0
